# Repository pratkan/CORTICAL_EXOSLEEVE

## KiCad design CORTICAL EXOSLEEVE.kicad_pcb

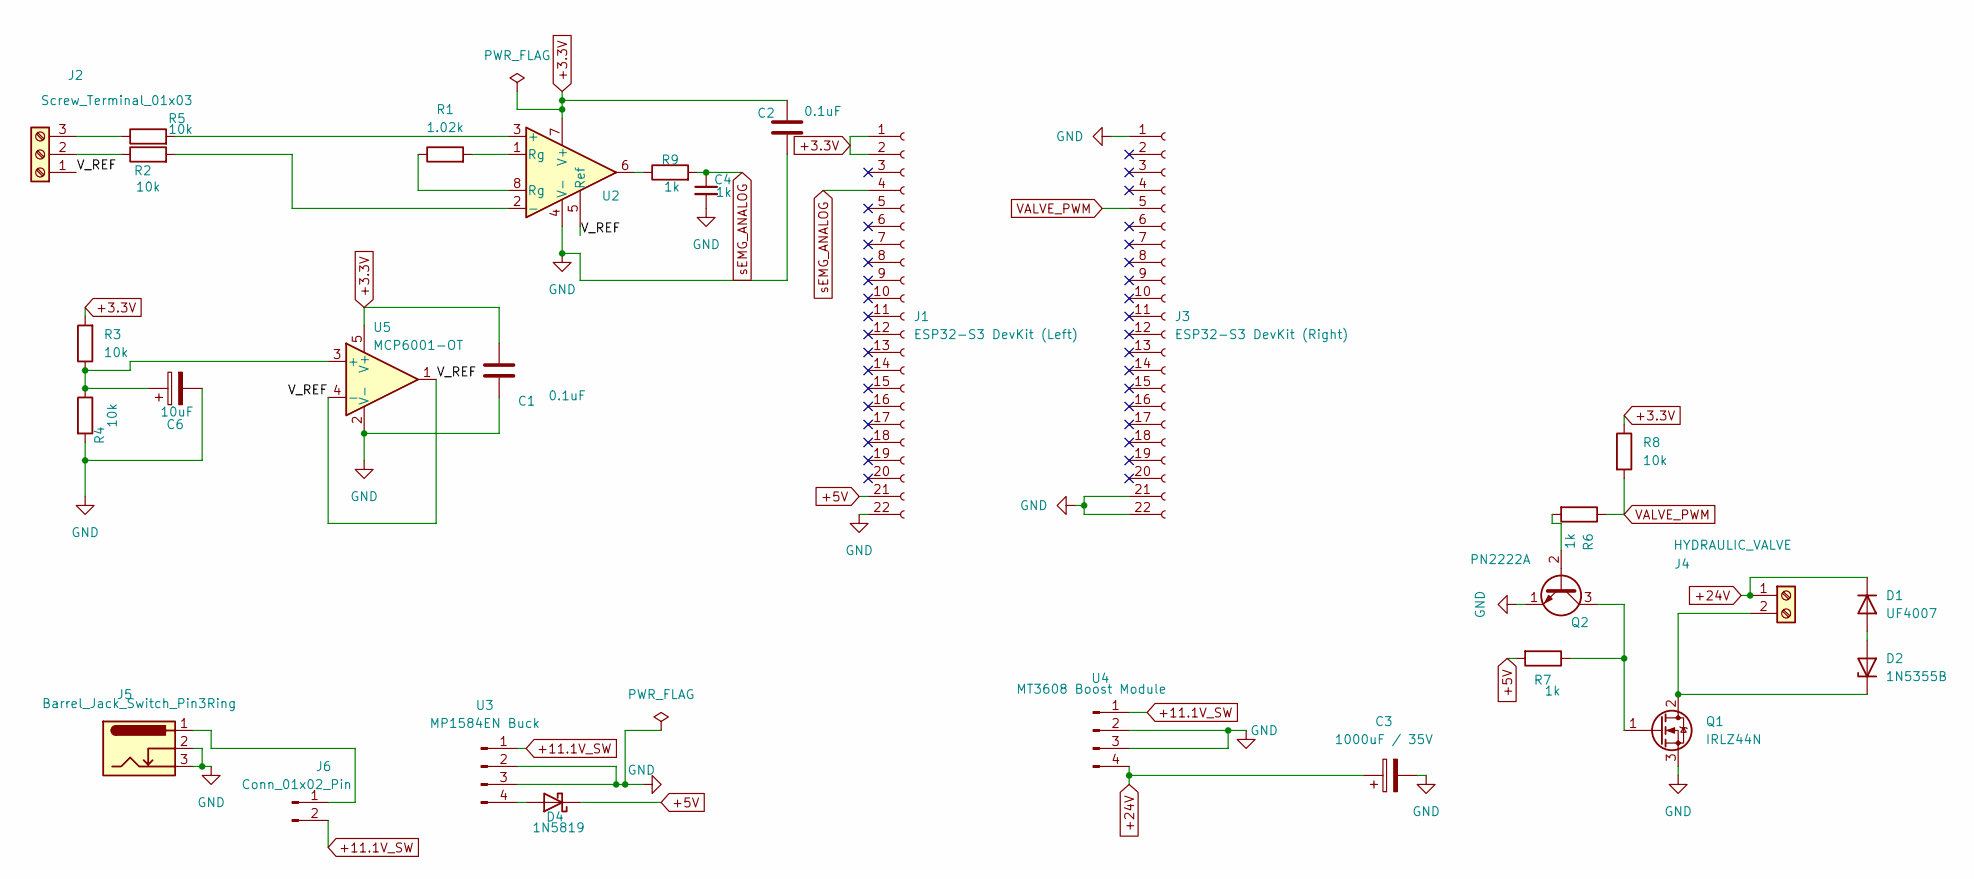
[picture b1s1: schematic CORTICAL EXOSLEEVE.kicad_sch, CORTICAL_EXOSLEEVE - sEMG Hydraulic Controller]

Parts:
C1, C2: 0.1uF; C_0805_2012Metric
C3: 1000uF / 35V; CP_Radial_D10.0mm_P5.00mm
C4: 1k; C_0805_2012Metric_Pad1.18x1.45mm_HandSolder
C6: 10uF; C_0805_2012Metric
D1: UF4007; D_DO-41_SOD81_P7.62mm_Horizontal
D2: 1N5355B; D_DO-201AD_P15.24mm_Horizontal
D4: 1N5819; D_SOD-123
J1: ESP32-S3 DevKit (Left); PinHeader_1x22_P2.54mm_Vertical
J2: Screw_Terminal_01x03; TerminalBlock_Phoenix_PT-1,5-3-5.0-H_1x03_P5.00mm_Horizontal
J3: ESP32-S3 DevKit (Right); PinHeader_1x22_P2.54mm_Vertical
J4: HYDRAULIC_VALVE; TerminalBlock_Phoenix_MKDS-1,5-2-5.08_1x02_P5.08mm_Horizont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
J5: Barrel_Jack_Switch_Pin3Ring; BarrelJack_Horizontal
J6: Conn_01x02_Pin; TerminalBlock_Phoenix_PT-1,5-2-5.0-H_1x02_P5.00mm_Horizontal
Q1: IRLZ44N; TO-220-3_Vertical
Q2: PN2222A; SOT-23
R1: 1.02k; R_0805_2012Metric_Pad1.20x1.40mm_HandSolder
R2, R3, R4, R5, R8: 10k; R_0805_2012Metric_Pad1.20x1.40mm_HandSolder
R6, R7, R9: 1k; R_0805_2012Metric_Pad1.20x1.40mm_HandSolder
U2: INA333xxDGK; MSOP-8_3x3mm_P0.65mm
U3: MP1584EN Buck; PinHeader_1x04_P2.54mm_Vertical
U4: MT3608 Boost Module; PinHeader_1x04_P2.54mm_Vertical
U5: MCP6001-OT; SOT-23-5

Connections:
+3.3V: C1.1, C2.1, J1.1, J1.2, R3.2, R8.1, U2.7 (V+), U5.5 (V+)
+5V: D4.1 (K), J1.21, R7.2
+11.1V_SW: J6.2, U3.1, U4.1
+24V: C3.1, D1.1 (K), J4.1, U4.4
/V_REF: J2.1, U2.5 (Ref), U5.1, U5.4 (-)
GND: C1.2, C2.2, C3.2, C4.2, C6.2, J1.22, J3.1, J3.21, J3.22, J5.2, J5.3, Q1.3 (S), Q2.1 (E), R4.2, U2.4 (V-), U3.2, U3.3, U4.2, U4.3, U5.2 (V-)
unnamed: D1.2 (A), D2.2 (A)
unnamed: D2.1 (K), J4.2, Q1.2 (D)
unnamed: D4.2 (A), U3.4
unnamed: J2.2, R2.1
unnamed: J2.3, R5.1
unnamed: J5.1, J6.1
unnamed: Q1.1 (G), Q2.3 (C), R7.1
unnamed: Q2.2 (B), R6.2
unnamed: R1.1, U2.8 (Rg)
unnamed: R1.2, U2.1 (Rg)
unnamed: R9.1, U2.6
unnamed: R5.2, U2.3 (+)
unnamed: R2.2, U2.2 (-)
unnamed: C6.1, R3.1, R4.1, U5.3 (+)
VALVE_PWM: J3.5, R6.1, R8.2
sEMG_ANALOG: C4.1, J1.4, R9.2

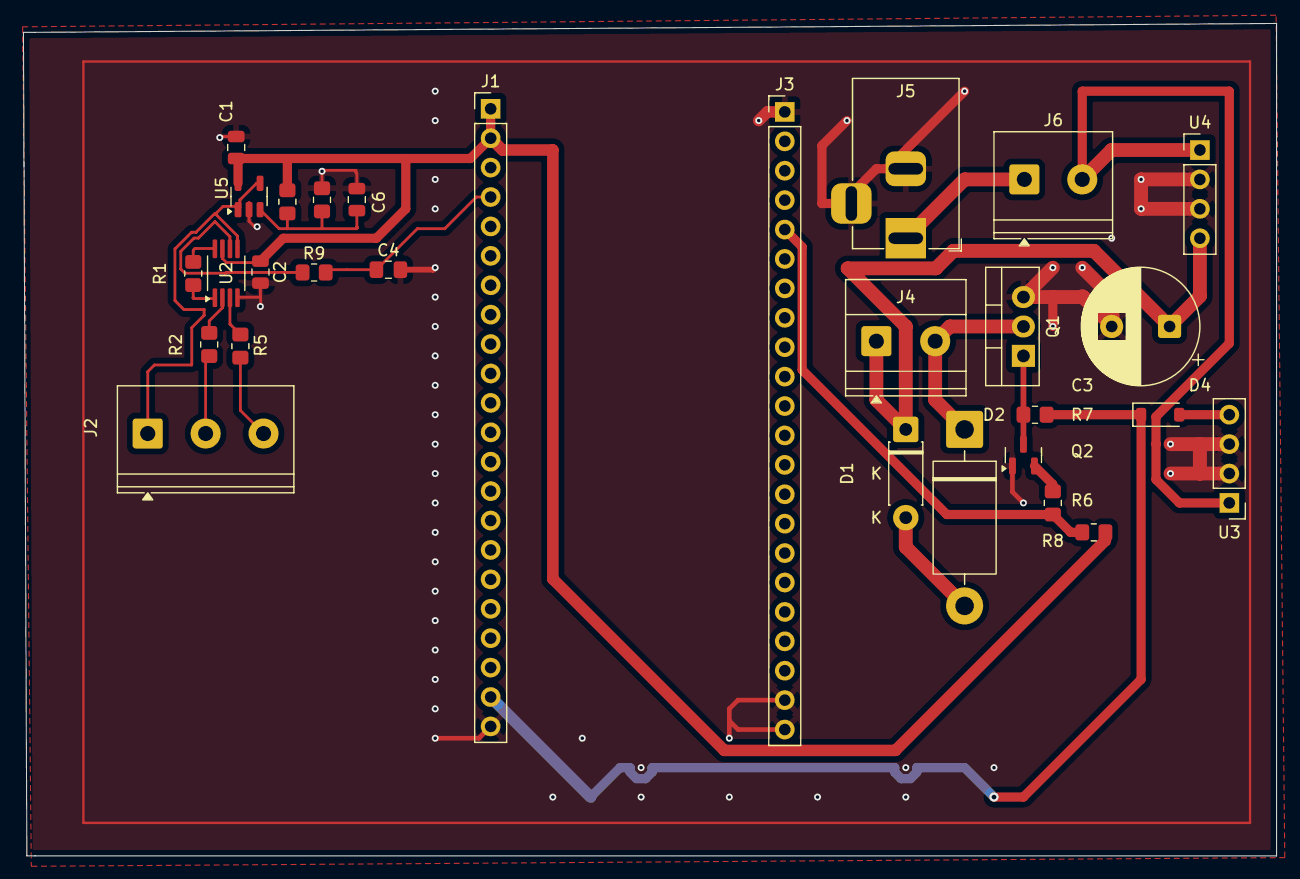
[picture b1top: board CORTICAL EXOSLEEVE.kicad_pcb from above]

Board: 2 copper layers, 108.2 x 71.9 mm, 29 parts (0 on the bottom side), 22 nets.

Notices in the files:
CORTICAL EXOSLEEVE.kicad_pcb:
License: CERN-OHL-S-v2 (Strongly Reciprocal)
SPDX-License-Identifier: CERN-OHL-S-v2
Copyright (c) 2026 Prat (pratkan)
